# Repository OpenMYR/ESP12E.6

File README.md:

IoT Motor Hardware: Stepper
==============================
by OpenMYR

[OpenMYR Homepage](http://www.OpenMYR.com/)

Software by Brandon Brown and Kyle Berezin

Hardware design by Chris Adams

Hardware licensed under CERN Hardware License Version 1.2

Software licensed under MIT License

This repository is the source files for hardware designed to drive a stepper motor with an ESP8266-based platform.

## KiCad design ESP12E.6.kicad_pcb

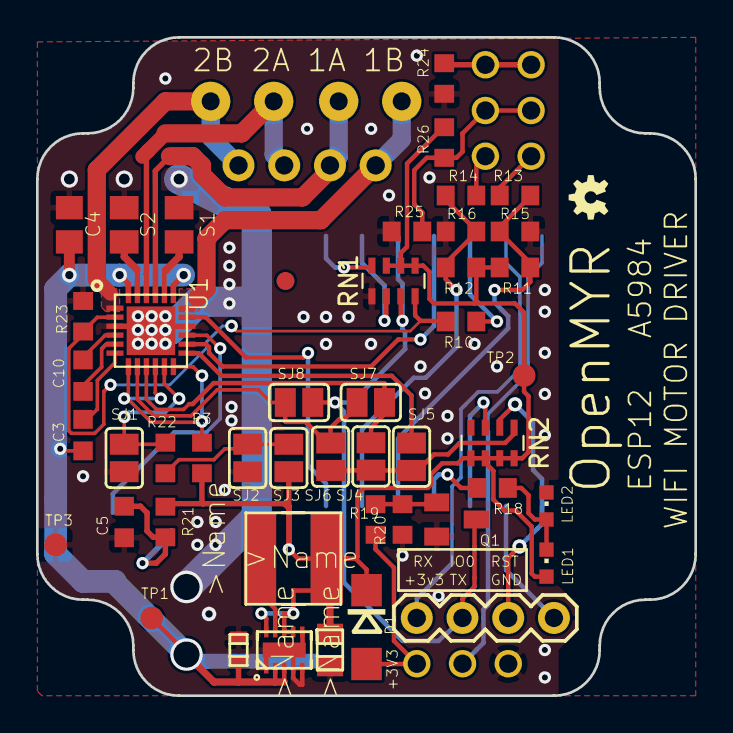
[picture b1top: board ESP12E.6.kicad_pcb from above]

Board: 2 copper layers, 36.6 x 36.6 mm, 58 parts (0 on the bottom side), 44 nets.

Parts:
C3, C10: 0.1uF; C0603K
C4: 4.7uF; C0805
C5: 0.47uF; C0603K
C8: 100uF; PANASONIC_D
CN1, CN2: 1X4-BIG; 1X04-BIG
D1: DIODE-DO214AC; DO214AC
FD1, FD2: FIDUCIAL; FIDUCIAL_1MM
J1, J4: 1X2-3.5MM
JP2, JP7, JP8: PINHD-1X3; 1X03
LED1, LED2: DNP; CHIPLED_0603
LOGO1: OSHW-LOGOMINI; OSHW-LOGO-MINI
Q1: MOSFET-NREFLOW; SOT23
R2: TC33X-2-103E; 35WR
R3, R19, R20, R21, R22: 10k; R0603
R10, R13, R14, R24, R26: 0; R0603
R11, R12, R15, R16, R18, R23, R25: DNP; R0603
RN1, RN2: R_Pack04; R_Array_Concave_4x0603
S1, S2: 0.1; M0805
SJ1, SJ2, SJ3, SJ4, SJ5, SJ6, SJ7, SJ8: SJ
TP1, TP2, TP3: PTR1B1,27; B1,27
U1: A5984; QFN-24
U$2: GRM21BR60J226ME39L; 0805
U$3: GRM188R61C225KE15D; 0603
U$4: SDR0503-100ML; SDR0503
U$5: TPS62177DQCR; R-PWSON-N10
X1: ESP-12

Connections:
+3V3: D1.C, LED1.A, R3.1, R11.1, R12.1, R21.2, R26.1, RN1.1, RN1.2, RN1.3, RN2.5, RN2.6, RN2.7, RN2.8, SJ3.2, TP2.TP, U$2.2, U$4.2, U$5.7, U$5.8, U$5.10, X1.8
/1A: CN2.2, J4.1, U1.P$21
/1B: CN2.1, J4.2, U1.P$18
/2A: CN2.3, J1.2, U1.P$22
/2B: CN2.4, J1.1, U1.P$1
/ADC: CN1.1, X1.2
/CH_PD: RN2.3, X1.3
/GPIO0: CN1.3, Q1.3, RN1.7, SJ8.1, X1.12
/GPIO2: RN1.6, X1.11
/GPIO4: R10.2, X1.14
/GPIO12: R12.2, R14.1, R16.2, X1.6
/GPIO14: R11.2, R13.1, R15.2, X1.5
/GPIO15: RN1.4, X1.10
/GPIO16: R18.1, X1.4
/N$3: JP7.1, R13.2
/N$11: C3.2, U1.P$6
/N$12: JP8.1, R14.2
/P3V3: D1.A, JP2.1, R19.2
/RESET: CN1.2, RN2.2, X1.1
/ROSC: R22.2, SJ1.2, U1.P$11
/RXD: CN1.4, X1.15
/SA: S1.1, U1.P$20
/SB: S2.1, U1.P$23
/SJ_3V3: RN2.1, SJ4.2, SJ5.2, SJ6.2
/TXD: JP2.2, X1.16
/VREF: R2.2, U1.P$15
/XDIR: U1.P$17, X1.7
/XENABLE: R10.1, R23.1, RN1.8, U1.P$2
/XMS1: SJ6.1, SJ7.1, SJ8.2, U1.P$8
/XMS2: SJ4.1, SJ7.2, U1.P$9
/XMS3: SJ5.1, U1.P$13
/XRESET: R3.2, U1.P$7, U1.P$10, U1.P$12
/XSTEP: U1.P$14, X1.13
GND: C4.2, C5.2, C8.-, JP2.3, LED2.C, Q1.2, R2.1, R15.1, R16.1, R20.1, R23.2, R24.1, R25.2, RN1.5, S1.2, S2.2, SJ1.1, SJ2.1, TP3.TP, U1.P$3, U1.P$16, U1.P$25, U$2.1, U$3.1, U$5.1, U$5.4, U$5.5, U$5.6, U$5.11, X1.9
unnamed: C5.1, R2.3, R21.1
unnamed: C10.1, U1.P$4
unnamed: C10.2, U1.P$5
unnamed: JP7.2, JP8.2, R25.1, R26.2
unnamed: JP7.3, JP8.3, R24.2
unnamed: LED1.C, LED2.A, R18.2
unnamed: Q1.1, R19.1, R20.2
unnamed: R22.1, SJ2.2, SJ3.1
unnamed: U$4.1, U$5.9
VCC: C3.1, C4.1, C8.+, TP1.TP, U1.P$19, U1.P$24, U$3.2, U$5.2, U$5.3

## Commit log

2016-04-03 :circus_tent: Added .gitattributes & .gitignore files
2016-04-03 First Commit
    Design 6:
    ESP12E with Allegro A5984
2016-04-06 GPIO pins repurposed
    GPIO 12 and 14 broken out to to pin headers for general use. Required
    that the MS section of board to be modified. GPIO0 now can control step
    mode between 0 and 32 micro-stepping.
2016-04-06 Additional Ignore files
    Added *.pro files to ignore file.
2016-05-08 Buck Regulator
    Prototype +3.3V DC buck regultaor. Based around TI TPS62177 IC.
2016-07-09 License Update
    Licensed under CERN OHL v.1.2 or later
2016-08-28 Power Isolation
    Separation between VMOT/+3V3 and +3V3/GND nets is increased. Rearranged
    R3,R21, U$3 and, U$2.
    Removed U$1 in the regulator schematic as it was not nessesary.
2016-10-15 PDF schematic generated
    PDF schematic added into Docs folder. Sch file modified to have
    schematic more presentable.
2018-05-20 //Lowered power via hole sizes to 18 AWG // Added ADC pin exposure
2018-05-24 PDF schematic updated
2018-10-18 Oct Update
    Power drill size change and placment of IO pin resistors
2018-11-23 A5984 QFN24
    Layout with QFN24 driver
2018-11-23 Updated Sch PDF
2018-11-23 KiCAD import with optimization
    ESP12.6 imported to KiCAD with A5984 QFN24 package and resistor array optimization.
2018-11-23 Update and added tracked files
2018-11-29 Removed solder paste from solder jumpers

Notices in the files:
ESP12E.6.kicad_pcb:
Copyright Christopher Adams 2016.
